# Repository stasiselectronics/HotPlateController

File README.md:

# HotPlateController
A simple ESP32 connected controller for a SMD reflow hot plate

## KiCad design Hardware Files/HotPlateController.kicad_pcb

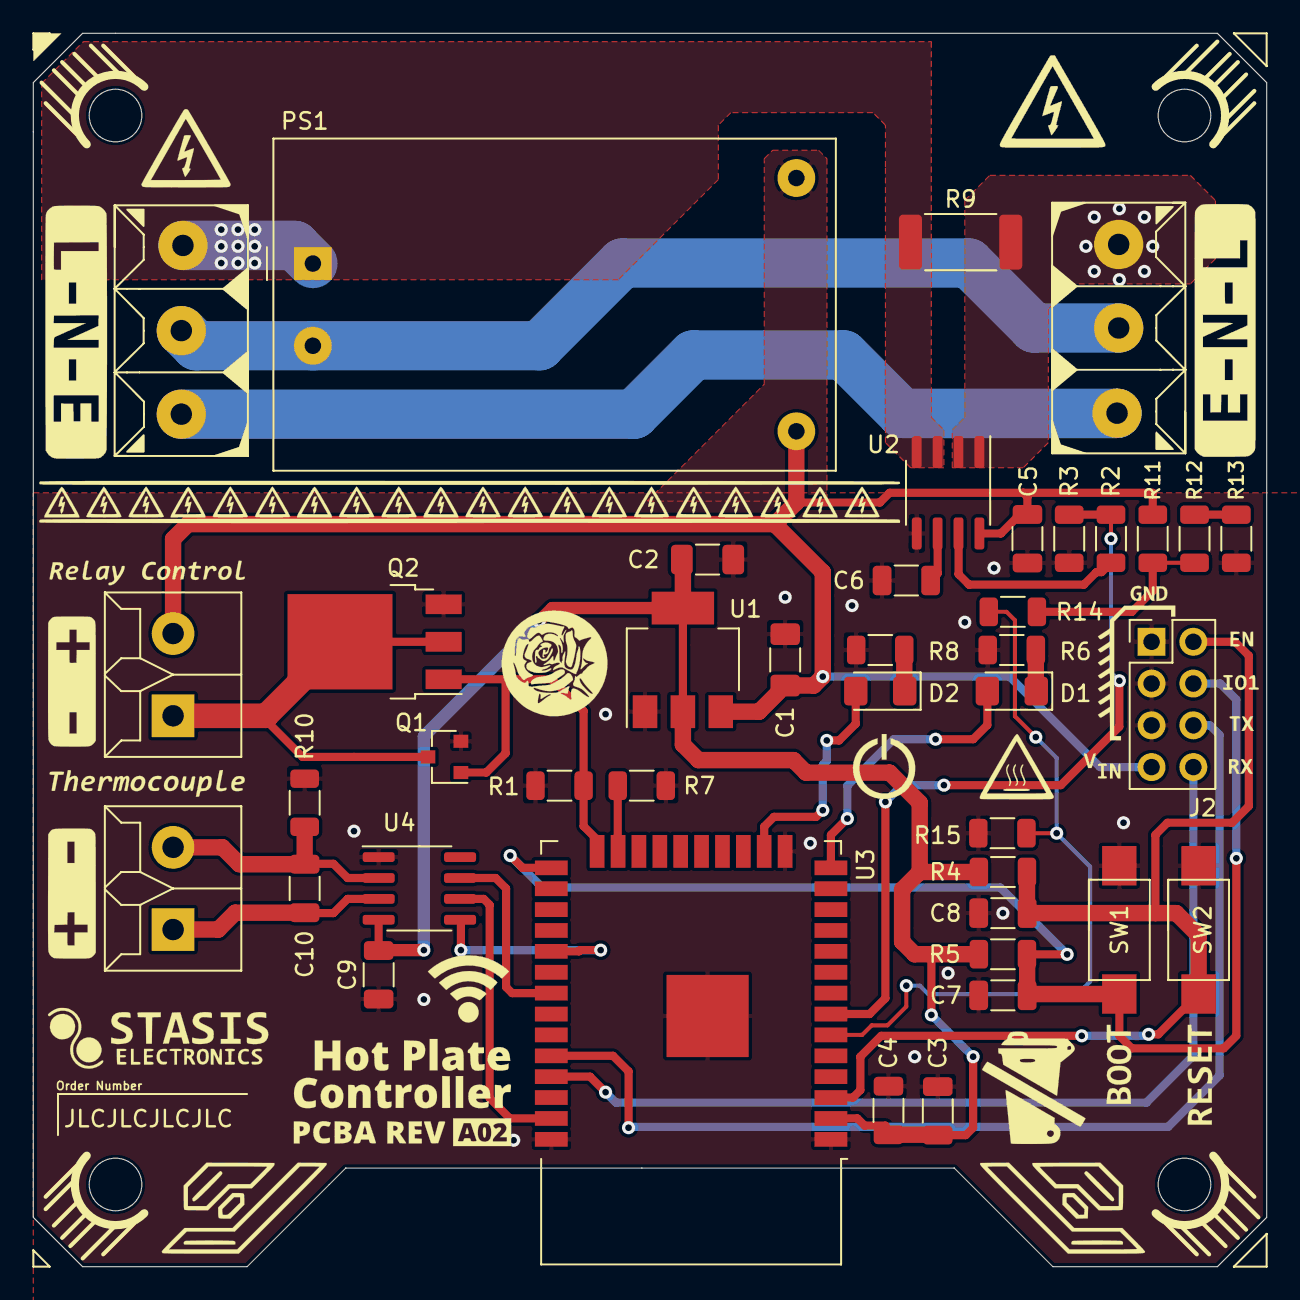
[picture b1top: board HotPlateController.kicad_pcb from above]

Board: 2 copper layers, 75.0 x 75.0 mm, 45 parts (0 on the bottom side), 29 nets.

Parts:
C1, C2: 220nF 50V; C_1206_3216Metric_Pad1.33x1.80mm_HandSolder
C3: 10uF 25V 10%; C_1206_3216Metric
C4, C5, C9: 1uF 50V; C_1206_3216Metric
C6, C7, C8: 1nF 50V; C_1206_3216Metric
C10: 10nF 50V; C_1206_3216Metric
D1: Green 3.0V; D_1206_3216Metric_Pad1.42x1.75mm_HandSolder
D2: Orange 2.0V; D_1206_3216Metric_Pad1.42x1.75mm_HandSolder
J1, J6: Conn_01x02; 1935161
J2: 0.100" 2x4 Header; PinHeader_2x04_P2.54mm_Vertical
J3, J4: Screw_Terminal_01x03; 1729131
M1, M2, M3, M4: Conn_01x01; MountingHole_3.2mm_M3_DIN965
PS1: HLK-PM01; Converter_ACDC_HiLink_HLK-PMxx
Q1: NMOS 60V 300mA; SOT-23
Q2: NMOS 60V 3A; TO-252-3_TabPin2
R1, R4, R5, R7: 10k 5% 0.25W; R_1206_3216Metric
R2, R11, R12, R13, R14: 1.37k 0.25W 1%; R_1206_3216Metric
R3, R15: 2.67k 0.25W 1%; R_1206_3216Metric
R6, R10: 0R; R_1206_3216Metric
R8: 43.2R; R_1206_3216Metric
R9: 0R; R_2512_6332Metric_Pad1.40x3.35mm_HandSolder
SW1, SW2: SPST; PTS636_SM25F_SMTR_LFS
U1: NCP1117ST33T3G; SOT-223-3_TabPin2
U2: ACS712xLCTR-20A; SOIC-8_3.9x4.9mm_P1.27mm
U3: ESP32-WROOM-32
U4: MAX31855KASA; SOIC-8_3.9x4.9mm_P1.27mm

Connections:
5V_adj: R14.2, R15.1, U3.6
+3V3: C2.1, C3.2, C4.1, C9.1, R4.1, R5.1, U1.2, U3.2, U4.4
+5V: C1.1, C5.2, J1.2, J2.7, PS1.4, R11.1, U1.3, U2.8
AC_Line_In: J4.3, R9.2, U2.1, U2.2
AC_Line_Out: J3.1, PS1.1, R9.1, U2.3, U2.4
AC_Neutral: J3.2, J4.2, PS1.2
EN: C8.2, J2.2, R4.2, SW2.1, U3.3
ESP32_SPI_MISO: U3.31, U4.7
ESP32_SPI_SCK: U3.29, U4.5
ESP32_SPI_TEMPSENSOR_1_CS: U3.37, U4.6
Earth: J3.3, J4.1
GND: C1.2, C2.2, C3.1, C4.2, C5.1, C6.2, C7.1, C8.1, C9.2, J2.1, J2.3, J2.5, PS1.3, Q1.2, Q2.3, R1.1, R3.2, R6.2, R7.2, R8.2, R10.2, R13.2, R15.2, SW1.2, SW2.2, U1.1, U2.5, U3.1, U3.15, U3.38, U3.39, U4.1
HotLED: D2.2, U3.16
IO0: C7.2, J2.4, R5.2, SW1.1, U3.25
unnamed: C6.1, U2.6
unnamed: C10.1, J6.1, U4.3
unnamed: C10.2, J6.2, R10.1, U4.2
unnamed: D1.1, R6.1
unnamed: D2.1, R8.1
unnamed: J1.1, Q1.3, Q2.2
unnamed: R2.1, U2.7
unnamed: R11.2, R12.1, R14.1
unnamed: R12.2, R13.1
PlateControl: Q1.1, Q2.1, R1.2, U3.24
StatusLED: D1.2, U3.14
U0TX_Active: R7.1, U3.23
USB_RX: J2.8, U3.35
USB_TX: J2.6, U3.34
V_Current_adj: R2.2, R3.1, U3.7

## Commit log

2021-01-11 add placeholder
2021-01-11 Update schematic
2021-01-11 add voltage regulator
2021-01-11 update ACS712 Circuit
2021-01-11 Fix footprints
2021-01-11 Add Relay level shifter
2021-01-11 Begin Layout
2021-01-11 add 3 pos terminal footprint
2021-01-11 Bulk routing
2021-01-12 Add artwork update PCBA Rev Silkscreen
2021-01-12 update item details
2021-01-12 Update Part Ordering Information
2021-01-13 Finalize board layout and art
2021-01-13 Finalize A01 Design
2021-01-13 Fix gerber output
2021-01-13 add jlcpcb order number location
2021-01-13 add jlcpcb ordering number
2021-01-22 Add 3D model
2021-02-03 Add test firmware
2021-02-03 Fix missing hot plate control trace
2021-02-03 Add test features
2021-02-03 update Thermocouple pin assignments
2021-02-03 Reroute Thermocouple IC traces
2021-02-19 Fix Thermocouple layout adjust pinouts to fix GPIO Issues adjust schematic formatting
2021-02-21 add 5v sense circuit Move around components Adjust board shape
2021-02-21 Finalize Layout Finalize Artwork Finalize Schematic
2021-03-16 add bottom artwork svg
2021-03-16 add bottom artwork
2021-03-16 add bottom artwork add part info to missing 10nF cap update BOM
2021-03-17 Generate A02 Board Fab Files
2021-04-10 Add BOM for A02 version
2021-04-11 A02 Assembly updates to check signals
2021-04-11 add thermocouple test code
2021-04-11 add mqtt version of firmware
2021-04-11 Add skeleton
2021-04-11 Add setup functionality, connects to mqtt
2021-04-11 add thermocouple sensing and reporting
2021-04-11 add led on wifi connect
2021-04-24 add wiring diagram
2021-04-25 update mqtt firmware
2021-05-01 Add interrupt based timers for non blocking LED blinking
2021-05-01 Add cutoff functionality
2021-07-09 remove wifi credentials
2021-07-09 begin changing provisioning method
2021-07-09 attempt to compile
2021-07-11 Add WiFi Provisioning example
2021-07-11 separate files for readability
2021-07-11 Add provisioning code
2021-07-11 fix files
2021-07-11 add even more files
2021-07-11 Finalize code for testing
2021-07-27 Add PID firmware
2021-08-13 add pdf schematic
2021-08-13 update schematic titleblock
2021-08-30 add some form of P control
